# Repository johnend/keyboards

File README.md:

# Keyboards

If you're here you're probably interested in either, my keybaord designs (🙌)
or, you're thinking about designing your own keyboard (also 🙌).

If you've done this before the footprints are in the libs folder as submodules.

If you haven't done this before there are lots of good resources available to
give you a headstart:

- [Designing a keybaord from scratch in KiCad](https://keyboarddweebs.net/2024/01/04/designing-a-keyboard-pcb-from-scratch-using-kicad/)
- [Joe Scotto's YouTube channel](https://www.youtube.com/@joe_scotto) - he also
  has a GitHub repo with a bunch of cool stuff in it. The link to that can be
found in the `libs` README.
- [Ben Vallack's YouTube channel](https://www.youtube.com/@BenVallack)
- [Flat Foot Fox's Ergogen Series](https://flatfootfox.com/ergogen-introduction/)

### A note on Ergogen
While Ergogen appears to be a simple way to design a mechanical keyboard, it can
be difficult to grep, especially given the docs are not easy to read and aren't
complete.

The Flat Foot Fox series is a good way to learn Ergogen though it does have some
limitations. Designing a split ergo in Ergogen seemed more convoluted that
necessary so I preferred to go straight into KiCad using the "Designing a
Keyboard from scratch" article and Joe Scotto's videos for reference.

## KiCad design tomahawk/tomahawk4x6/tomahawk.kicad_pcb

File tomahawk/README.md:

# Tomahawk Split Ergo Keyboard

**N.B. The content of what is in this repo is in the early design phase, and
so should not be considered remotely usable at this point.**

The Tomahawk is a split ergo keyboard designed to be low profile, and have a
large number of thumb keys.

The main intention for me was to ensure I could mirror my Cyboard Imprint build
as closely as possible while making something low profile and portable (because
Dactly type keyboards are great, but also massive).

## Features

- Split ergo design with USB connectivity (maybe wireless in the future),
- 6 thumbs keys in a two row, three column, layout, that allows for lots of
  thumb use,
- An additional **mod row** that allows for mapping ctrl, alt, and super
  separately (or to whatever you want),
- Large memory with support for many layers
- Per key RGB (optional),
- RGB backlighting (optional),

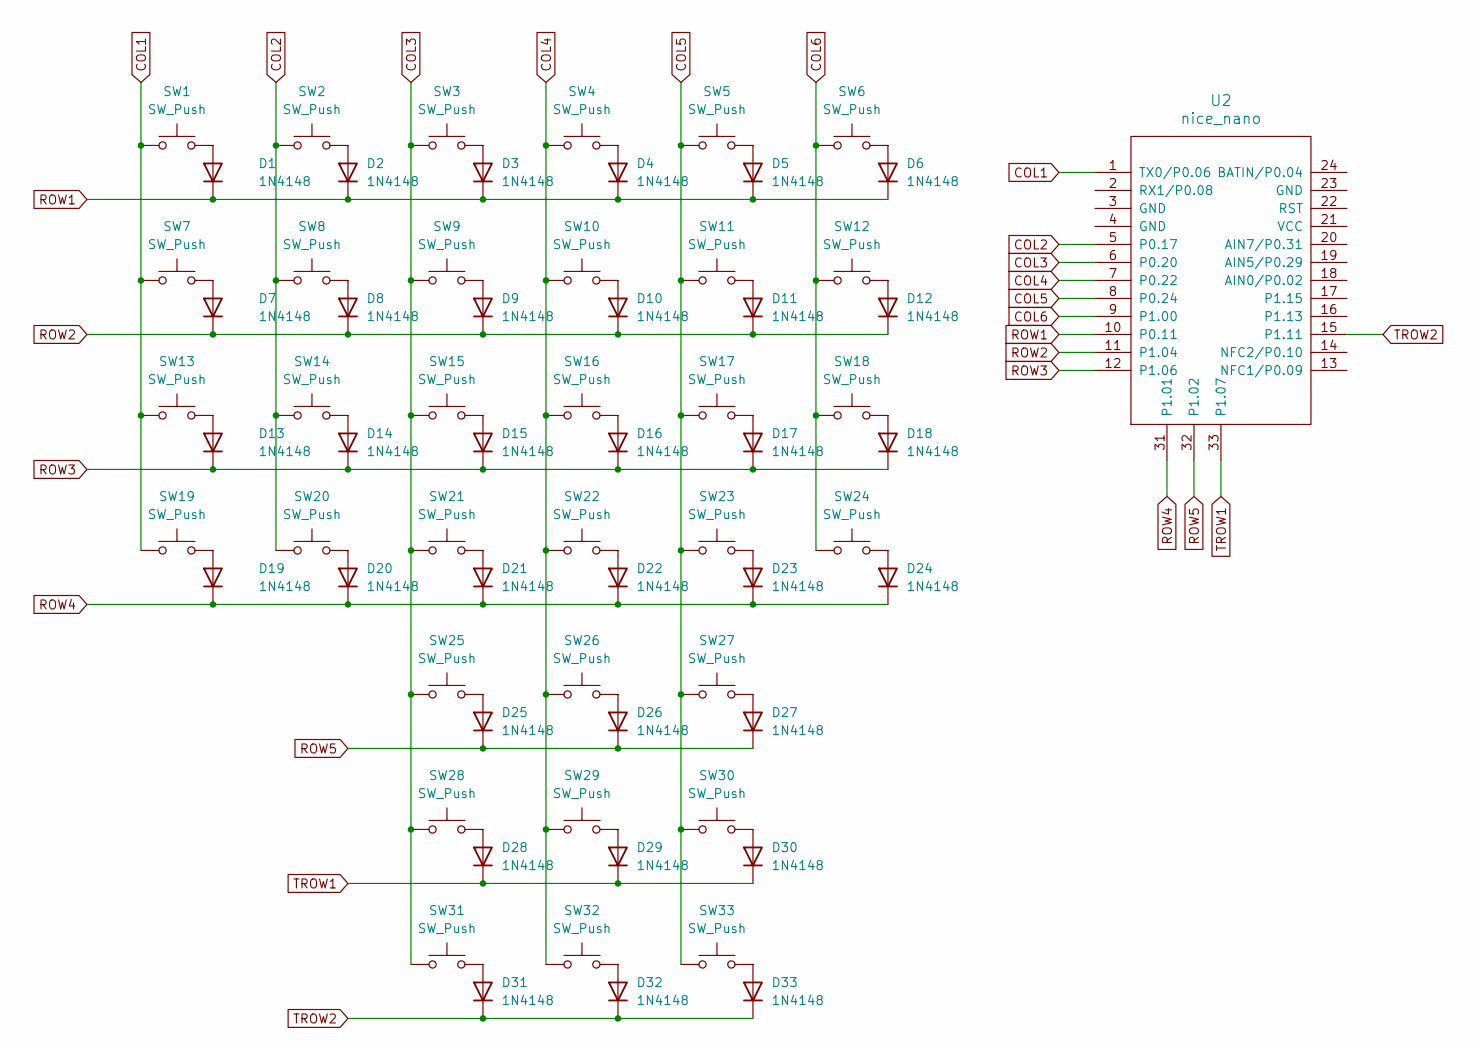
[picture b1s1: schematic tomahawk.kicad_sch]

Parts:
D1, D2, D3, D4, D5, D6, D7, D8, D9, D10, D11, D12, D13, D14, D15, D16, D17, D18, D19, D20, D21, D22, D23, D24, D25, D26, D27, D28, D29, D30, D31, D32, D33: 1N4148; D_SOD-123
SW1, SW2, SW3, SW4, SW5, SW6, SW7, SW8, SW9, SW10, SW11, SW12, SW13, SW14, SW15, SW16, SW17, SW18, SW19, SW20, SW21, SW22, SW23, SW24, SW25, SW26, SW27, SW28, SW29, SW30, SW31, SW32, SW33: SW_Push; Hotswap_Choc_V1V2_1.00u
U2: nice_nano

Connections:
COL1: SW1.1, SW7.1, SW13.1, SW19.1, U2.1 (TX0/P0.06)
COL2: SW2.1, SW8.1, SW14.1, SW20.1, U2.5 (P0.17)
COL3: SW3.1, SW9.1, SW15.1, SW21.1, SW25.1, SW28.1, SW31.1, U2.6 (P0.20)
COL4: SW4.1, SW10.1, SW16.1, SW22.1, SW26.1, SW29.1, SW32.1, U2.7 (P0.22)
COL5: SW5.1, SW11.1, SW17.1, SW23.1, SW27.1, SW30.1, SW33.1, U2.8 (P0.24)
COL6: SW6.1, SW12.1, SW18.1, SW24.1, U2.9 (P1.00)
unnamed: D1.2 (A), SW1.2
unnamed: D2.2 (A), SW2.2
unnamed: D3.2 (A), SW3.2
unnamed: D4.2 (A), SW4.2
unnamed: D5.2 (A), SW5.2
unnamed: D6.2 (A), SW6.2
unnamed: D7.2 (A), SW7.2
unnamed: D8.2 (A), SW8.2
unnamed: D9.2 (A), SW9.2
unnamed: D10.2 (A), SW10.2
unnamed: D11.2 (A), SW11.2
unnamed: D12.2 (A), SW12.2
unnamed: D13.2 (A), SW13.2
unnamed: D14.2 (A), SW14.2
unnamed: D15.2 (A), SW15.2
unnamed: D16.2 (A), SW16.2
unnamed: D17.2 (A), SW17.2
unnamed: D18.2 (A), SW18.2
unnamed: D19.2 (A), SW19.2
unnamed: D20.2 (A), SW20.2
unnamed: D21.2 (A), SW21.2
unnamed: D22.2 (A), SW22.2
unnamed: D23.2 (A), SW23.2
unnamed: D24.2 (A), SW24.2
unnamed: D25.2 (A), SW25.2
unnamed: D26.2 (A), SW26.2
unnamed: D27.2 (A), SW27.2
unnamed: D28.2 (A), SW28.2
unnamed: D29.2 (A), SW29.2
unnamed: D30.2 (A), SW30.2
unnamed: D31.2 (A), SW31.2
unnamed: D32.2 (A), SW32.2
unnamed: D33.2 (A), SW33.2
ROW1: D1.1 (K), D2.1 (K), D3.1 (K), D4.1 (K), D5.1 (K), D6.1 (K), U2.10 (P0.11)
ROW2: D7.1 (K), D8.1 (K), D9.1 (K), D10.1 (K), D11.1 (K), D12.1 (K), U2.11 (P1.04)
ROW3: D13.1 (K), D14.1 (K), D15.1 (K), D16.1 (K), D17.1 (K), D18.1 (K), U2.12 (P1.06)
ROW4: D19.1 (K), D20.1 (K), D21.1 (K), D22.1 (K), D23.1 (K), D24.1 (K), U2.31 (P1.01)
ROW5: D25.1 (K), D26.1 (K), D27.1 (K), U2.32 (P1.02)
TROW1: D28.1 (K), D29.1 (K), D30.1 (K), U2.33 (P1.07)
TROW2: D31.1 (K), D32.1 (K), D33.1 (K), U2.15 (P1.11)

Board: 2 copper layers, 67 parts (33 on the bottom side), 46 nets, no tracks yet.

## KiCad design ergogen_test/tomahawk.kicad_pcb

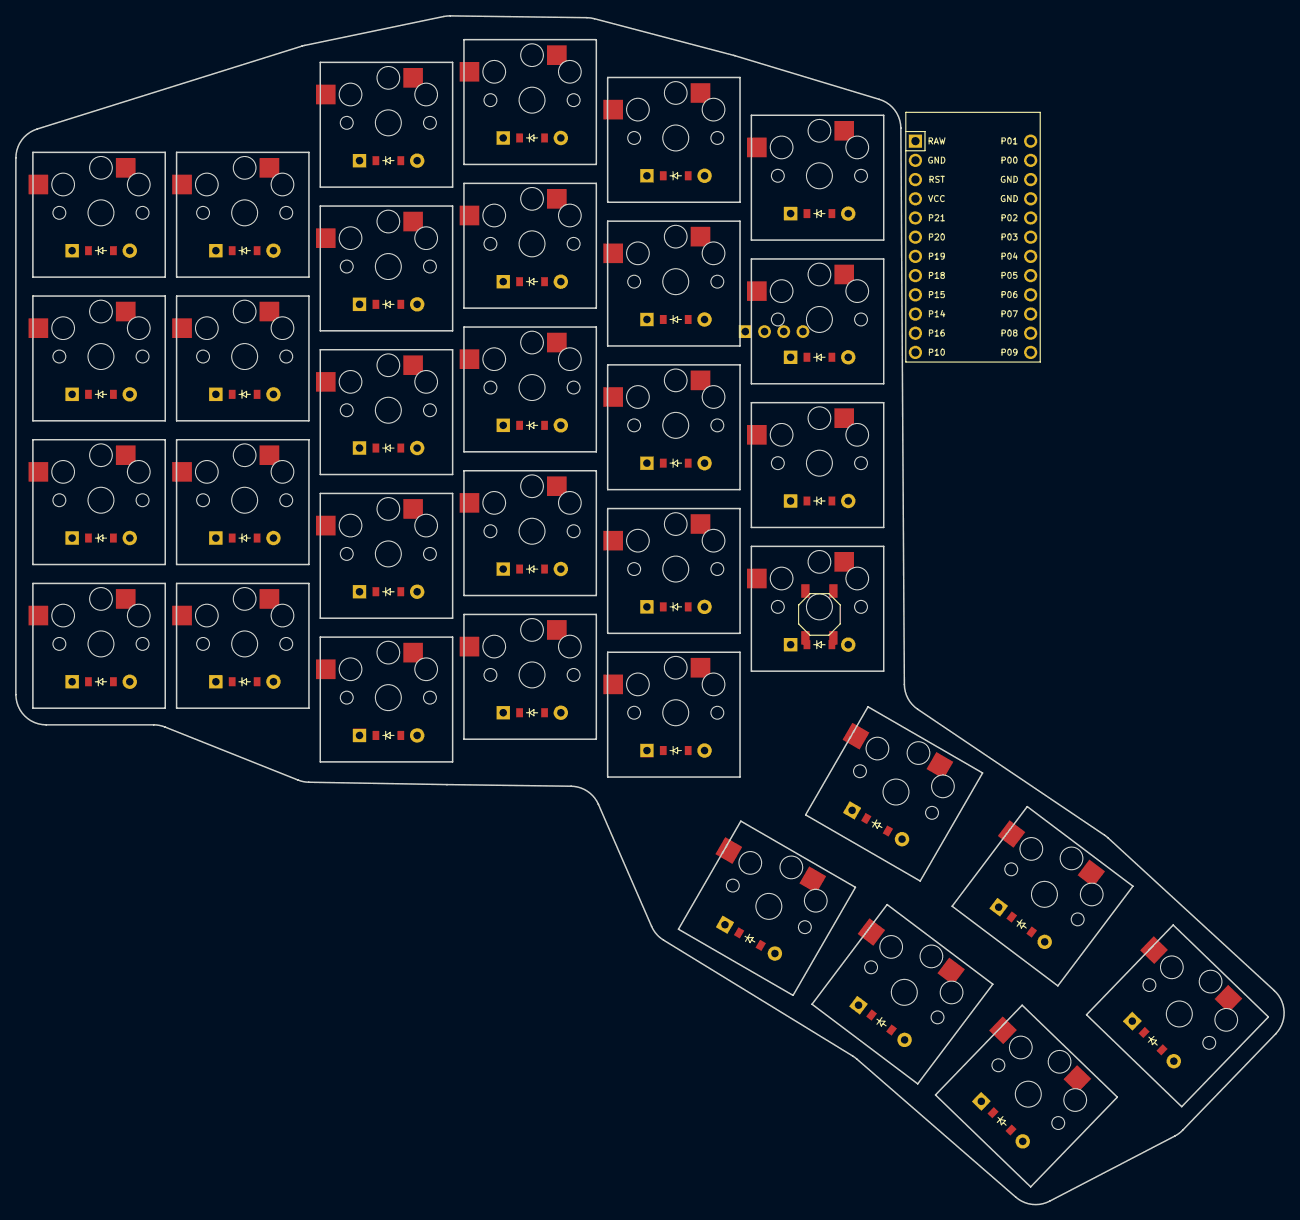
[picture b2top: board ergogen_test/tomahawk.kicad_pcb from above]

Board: 2 copper layers, 167.7 x 157.2 mm, 69 parts (0 on the bottom side), 32 nets, no tracks yet.

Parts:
B1: SW_TACT_ALPS_SKQGABE010
D1, D2, D3, D4, D5, D6, D7, D8, D9, D10, D11, D12, D13, D14, D15, D16, D17, D18, D19, D20, D21, D22, D23, D24, D25, D26, D27, D28, D29, D30, D31, D32, D33: ComboDiode
MCU1: ProMicro
OLED1: OLED; OLED_headers
S1, S2, S3, S4, S5, S6, S7, S8, S9, S10, S11, S12, S13, S14, S15, S16, S17, S18, S19, S20, S21, S22, S23, S24, S25, S26, S27, S28, S29, S30, S31, S32, S33: PG1350

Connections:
GND: B1.1, MCU1.2, MCU1.15, MCU1.16, OLED1.1
P2: MCU1.17, OLED1.4
P3: MCU1.18, OLED1.3
RST: B1.2, MCU1.3
VCC: MCU1.4, OLED1.2
index_bottom: D20.2, S20.2
index_home: D21.2, S21.2
index_mod: D19.2, S19.2
index_num: D23.2, S23.2
index_top: D22.2, S22.2
inner_bottom: D24.2, D28.2, S24.2, S28.2
inner_home: D25.2, S25.2
inner_num: D27.2, S27.2
inner_top: D26.2, D29.2, S26.2, S29.2
middle_bottom: D15.2, D30.2, S15.2, S30.2
middle_home: D16.2, S16.2
middle_mod: D14.2, S14.2
middle_num: D18.2, S18.2
middle_top: D17.2, D31.2, S17.2, S31.2
outer_bottom: D1.2, D32.2, S1.2, S32.2
outer_home: D2.2, S2.2
outer_num: D4.2, S4.2
outer_top: D3.2, D33.2, S3.2, S33.2
pinky_bottom: D5.2, S5.2
pinky_home: D6.2, S6.2
pinky_num: D8.2, S8.2
pinky_top: D7.2, S7.2
ring_bottom: D10.2, S10.2
ring_home: D11.2, S11.2
ring_mod: D9.2, S9.2
ring_num: D13.2, S13.2
ring_top: D12.2, S12.2

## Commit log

2025-03-22 keyboards: initial commit
    contains previous work on a design
2025-03-23 add submodules
2025-03-23 submodules readme
2025-03-23 main readme
2025-03-23 updated footprints and pcb
2025-03-24 added gitignore
2025-03-24 updated layout and pcb
    - still need to work on the thumb cluster
2025-03-24 rough tracks
2025-03-25 WIP: need to fix thumb cluster
2025-03-27 WIP: aligned layout, updated design and net class rules
2025-03-28 wip updated diode positioning, and placed thumb cluster
2025-04-02 some more
